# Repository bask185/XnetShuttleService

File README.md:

# XpressNet based shuttle moduley

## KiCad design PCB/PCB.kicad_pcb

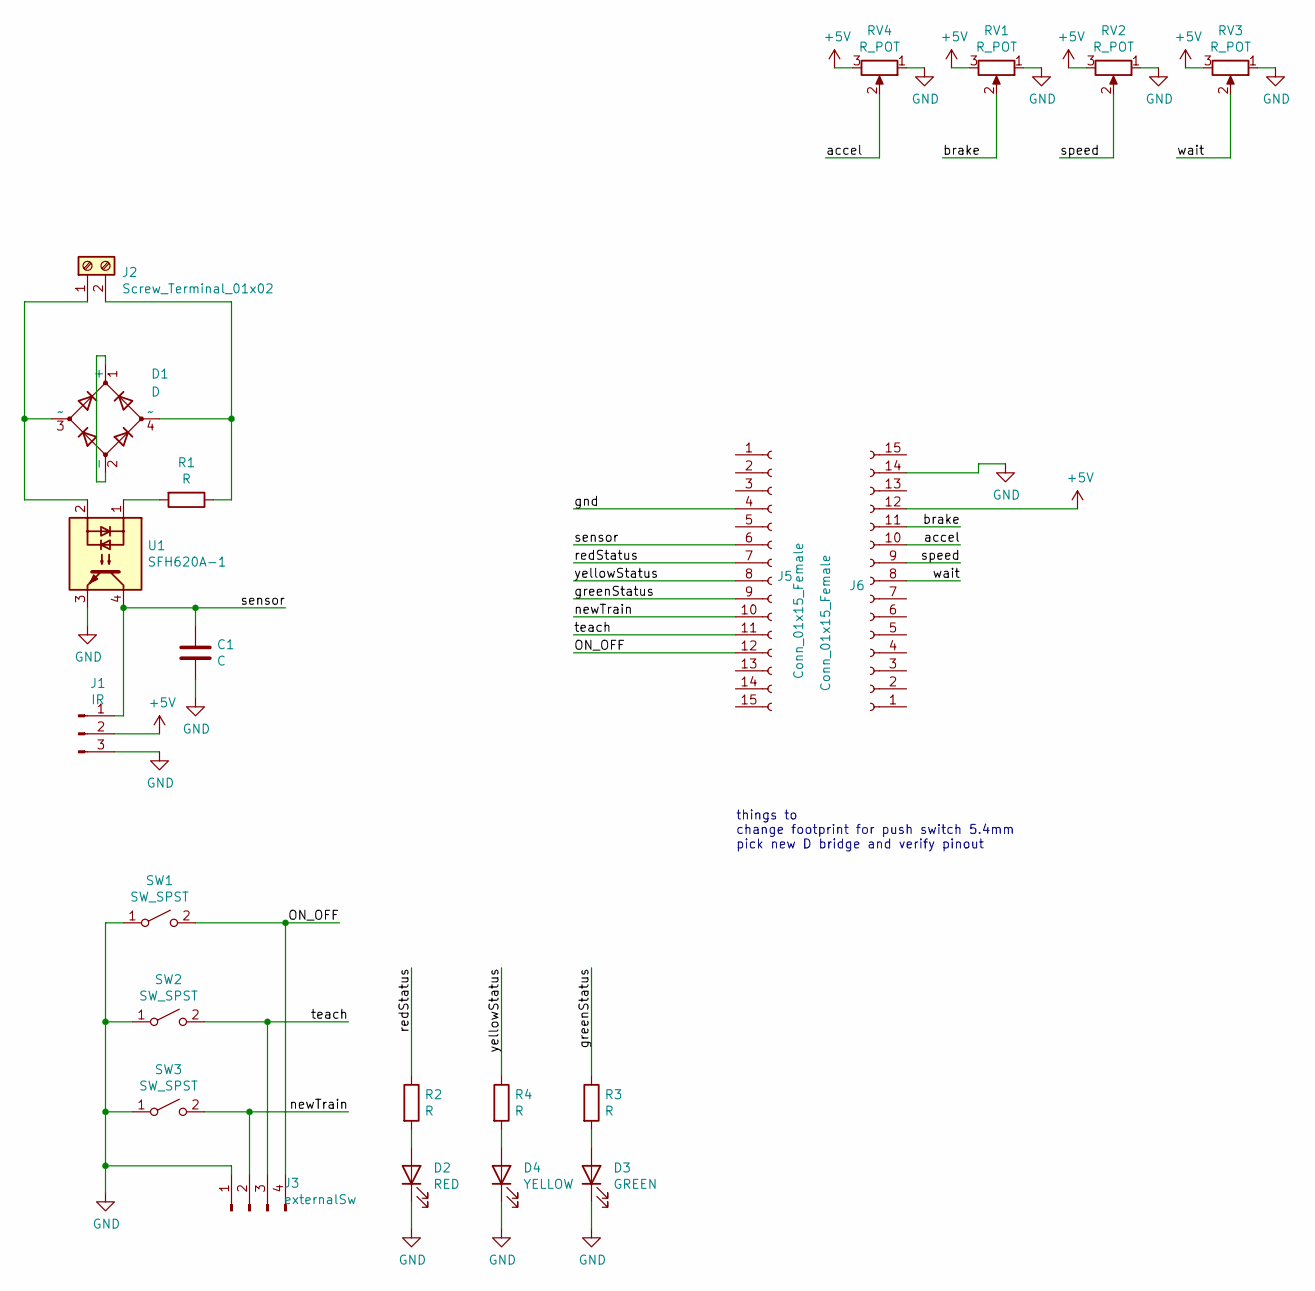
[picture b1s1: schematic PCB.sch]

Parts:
C1: C; C_Disc_D3.0mm_W1.6mm_P2.50mm
D1: D; Diode_Bridge_DIP-4_W7.62mm_P5.08mm
D2: RED; LED_D3.0mm
D3: GREEN; LED_D3.0mm
D4: YELLOW; LED_D3.0mm
J1: IR; PinHeader_1x03_P2.54mm_Vertical
J2: Screw_Terminal_01x02; TerminalBlock_Phoenix_MKDS-1,5-2-5.08_1x02_P5.08mm_Horizont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
J3: externalSw; PinHeader_1x04_P2.54mm_Vertical
J5, J6: Conn_01x15_Female; PinSocket_1x15_P2.54mm_Vertical
R1, R2, R3, R4: R; R_Axial_DIN0204_L3.6mm_D1.6mm_P7.62mm_Horizontal
RV1, RV2, RV3, RV4: R_POT; Potentiometer_Runtron_RM-065_Vertical
SW1, SW2, SW3: SW_SPST; SW_PUSH_6mm_H4.3mm
U1: SFH620A-1; DIP-4_W7.62mm

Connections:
+5V: J1.2, J6.12, RV1.3, RV2.3, RV3.3, RV4.3
/ON_OFF: J3.4, J5.12, SW1.2 (B)
/accel: J6.10, RV4.2
/brake: J6.11, RV1.2
/gnd: J5.4
/greenStatus: J5.9, R3.1
/newTrain: J3.2, J5.10, SW3.2 (B)
/redStatus: J5.7, R2.1
/sensor: C1.1, J1.1, J5.6, U1.4
/speed: J6.9, RV2.2
/teach: J3.3, J5.11, SW2.2 (B)
/wait: J6.8, RV3.2
/yellowStatus: J5.8, R4.1
GND: C1.2, D2.1 (K), D3.1 (K), D4.1 (K), J1.3, J3.1, J6.14, RV1.1, RV2.1, RV3.1, RV4.1, SW1.1 (A), SW2.1 (A), SW3.1 (A), U1.3
unnamed: D1.1 (+), D1.2 (-)
unnamed: D1.3 (~~), J2.1, U1.2
unnamed: D1.4 (~~), J2.2, R1.1
unnamed: D2.2 (A), R2.2
unnamed: D3.2 (A), R3.2
unnamed: D4.2 (A), R4.2
unnamed: R1.2, U1.1

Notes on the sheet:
things to change footprint for push switch 5.4mm pick new D bridge and verify pinout

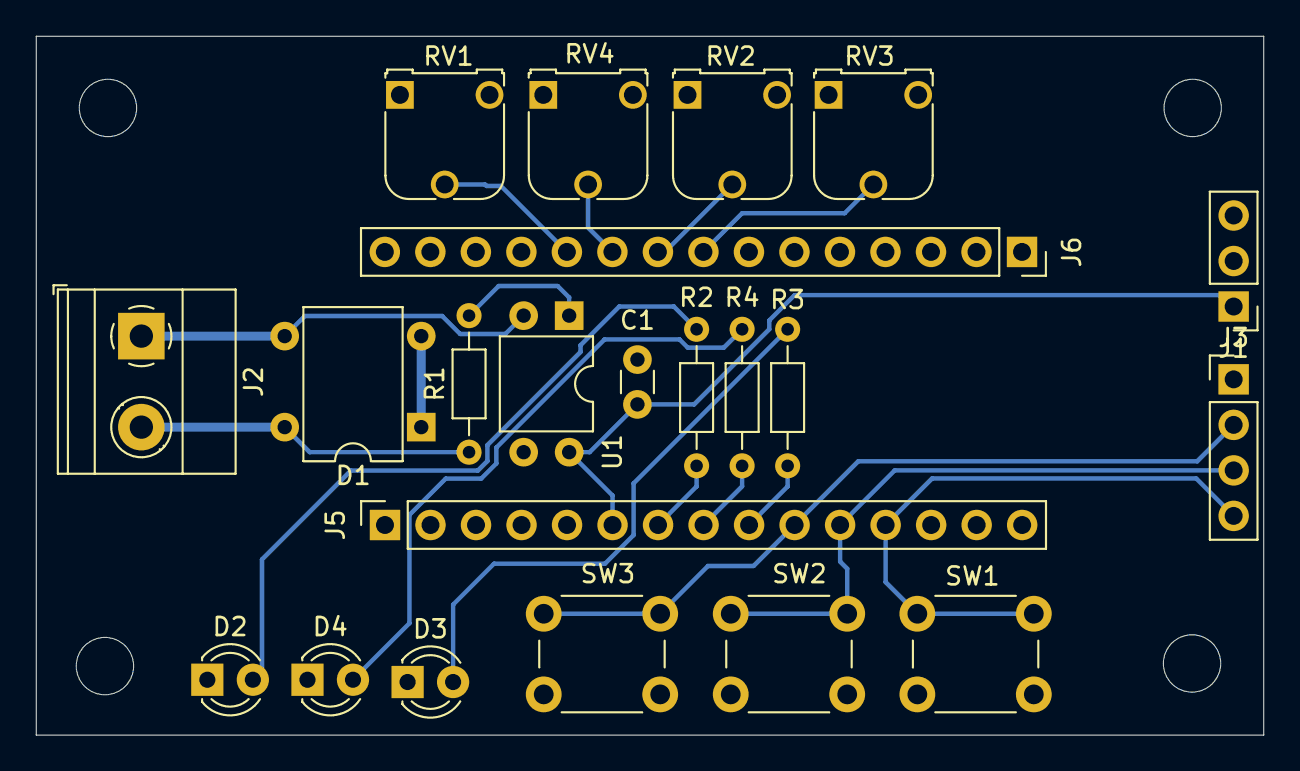
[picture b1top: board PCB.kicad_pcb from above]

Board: 2 copper layers, 68.5 x 39.0 mm, 22 parts (0 on the bottom side), 20 nets.

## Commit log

2022-03-09 added some blinkLights here and there. The control mode, with buttons n all need to be made, as well as the actual train controlling
2022-03-10 some minor changes
2022-03-10 added pre-defined point streets
2022-03-10 added some comments, fixed event and modes for a part
